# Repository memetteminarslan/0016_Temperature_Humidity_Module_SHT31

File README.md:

# 0016_Temperature_Humidity_Module_SHT31

You are seeing a large number of widely used Temperature Humidity modules in electronic development kits. More information coming soon...

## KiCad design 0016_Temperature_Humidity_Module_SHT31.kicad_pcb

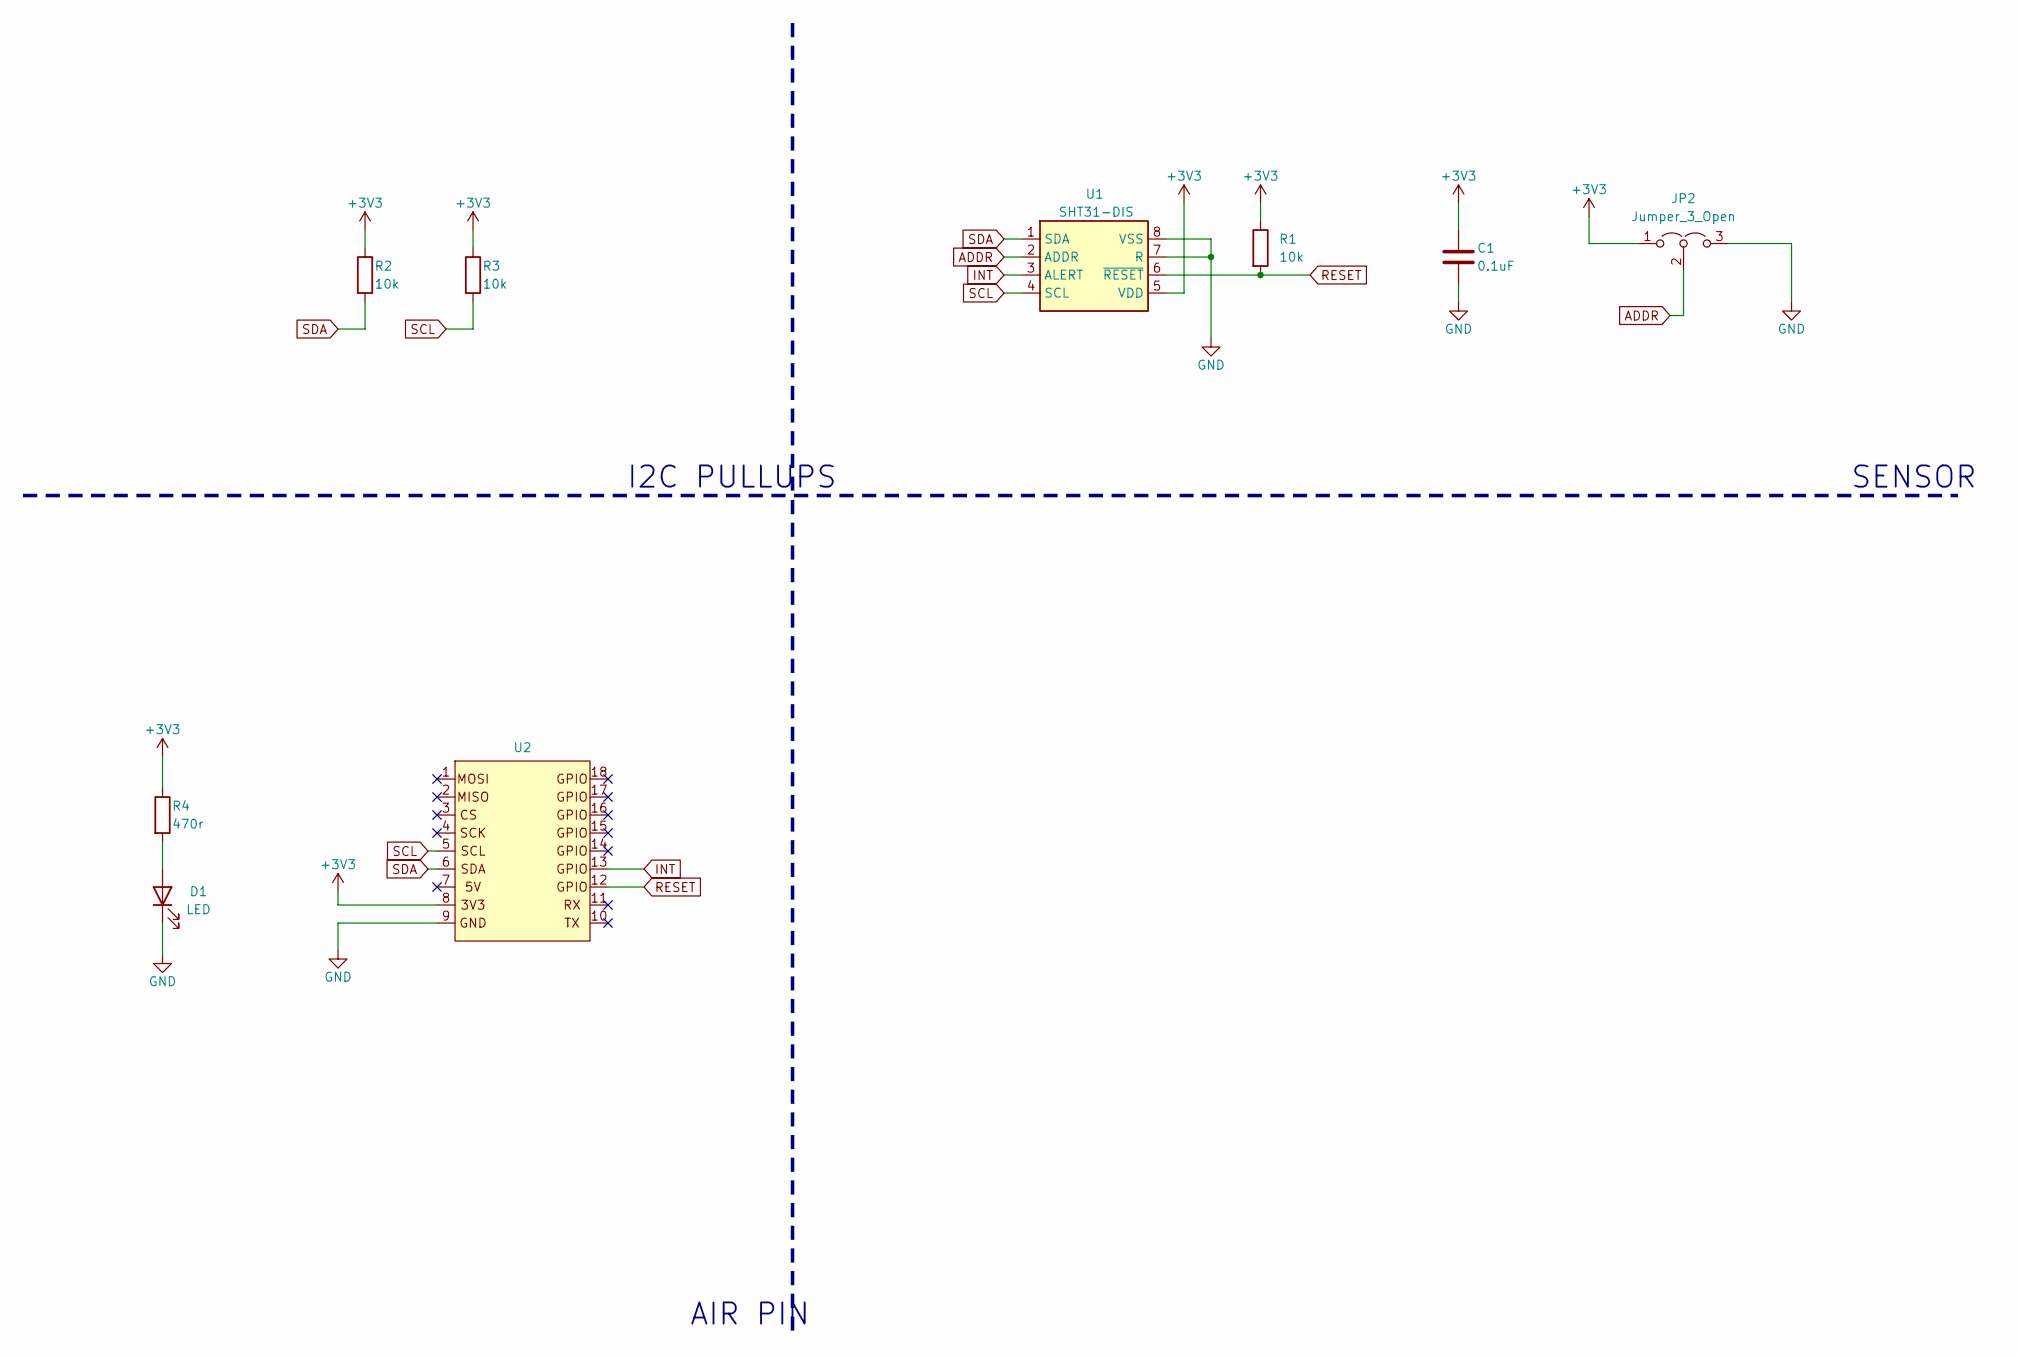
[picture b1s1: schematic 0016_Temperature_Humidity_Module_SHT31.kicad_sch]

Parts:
C1: 0.1uF; C_0805_2012Metric
D1: LED; LED_0805_2012Metric
JP2: Jumper_3_Open; SolderJumper-3_P1.3mm_Open_Pad1.0x1.5mm
R1, R2, R3: 10k; R_0805_2012Metric
R4: 470r; R_0805_2012Metric
U1: SHT31-DIS; Sensirion_DFN-8-1EP_2.5x2.5mm_P0.5mm_EP1.1x1.7mm
U2: pin_header

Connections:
+3V3: C1.1, JP2.1 (A), R1.1, R2.1, R3.1, R4.1, U1.5 (VDD), U2.8
ADDR: JP2.2 (C), U1.2 (ADDR)
GND: C1.2, D1.1 (K), JP2.3 (B), U1.7 (R), U1.8 (VSS), U1.9 (VSS), U2.9
INT: U1.3 (ALERT), U2.13
unnamed: D1.2 (A), R4.2
RESET: R1.2, U1.6 (~RESET), U2.12
SCL: R3.2, U1.4 (SCL), U2.5
SDA: R2.2, U1.1 (SDA), U2.6

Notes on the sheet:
AIR PIN
SENSOR
I2C PULLUPS

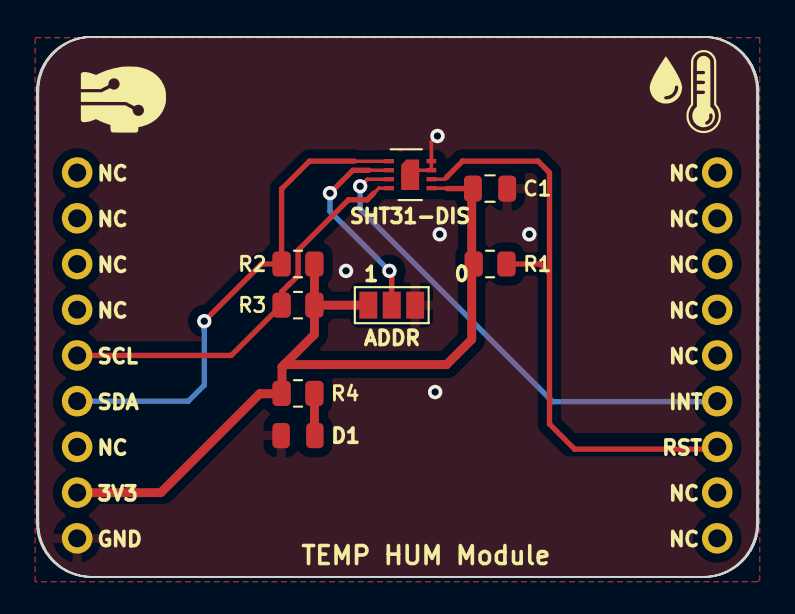
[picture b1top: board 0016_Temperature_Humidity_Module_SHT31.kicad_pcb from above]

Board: 2 copper layers, 40.1 x 30.0 mm, 9 parts (0 on the bottom side), 8 nets.
